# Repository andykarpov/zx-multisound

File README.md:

## ZX-MultiSound
Sound card for ZX Spectrum (NemoBus).

### Tech specs
* TurboSound FM (2xYM2203)
* General Sound (16MHz, 1024Kb of RAM)
* SAA1099 (use port #FF/#1FF to access SAA chip, write #F7/#FF to #FFFD port to enable/disable SAA)
* SounDrive (ports #0F, #1F, #4F, #5F)
* MIDI synthesizer (controlled via YM(AY) chip - compatible with ZX Spectrum 128K / ZXUNO)
* Low profile PCB: 170x64mm
* 5V and 12V power required
* 4x 1-bit digital DACs for GS and SounDrive

### Changelog & current status
* Rev.A - first release. Please note the [errata](pcb/rev.A/ERRATA.txt);
* Rev.A1 - fixed known rev.A issues. Please note the [errata](pcb/rev.A1/ERRATA.txt).
* Rev.A2:
    * Fixed Z80 clocking - added buffer;
    * Fixed 3.5mm jack footprint swapped left-right channels;
    * Fixed misplaced R20 and R34 labels on silkscreen;
    * 74LVC1G125DB replaced by 74AHCT1G125DB;
    * C3,C5,C17,C18 slightly moved left;
    * Added ledge on edge connector;
    * Improved SAM2695 footprint for hand soldering.
* Rev.KA2:
    * Single SRAM chip 2mb

Sound card has been tested only with ZX Evolution. You can use it with another computer at your own risk.

### Related projects
* Turbo Sound FM - [link](http://www.nedopc.com/TURBOSOUND/ts-fm.php)
* ZXM-SoundCard - [link](http://micklab.ru/My%20Soundcard/ZXMSoundCard.htm)
* ZXM-GeneralSound - [link](http://micklab.ru/My%20Soundcard/ZXMGeneralSound.htm)
* NeoGS - [link](http://www.nedopc.com/gs/ngs.php)

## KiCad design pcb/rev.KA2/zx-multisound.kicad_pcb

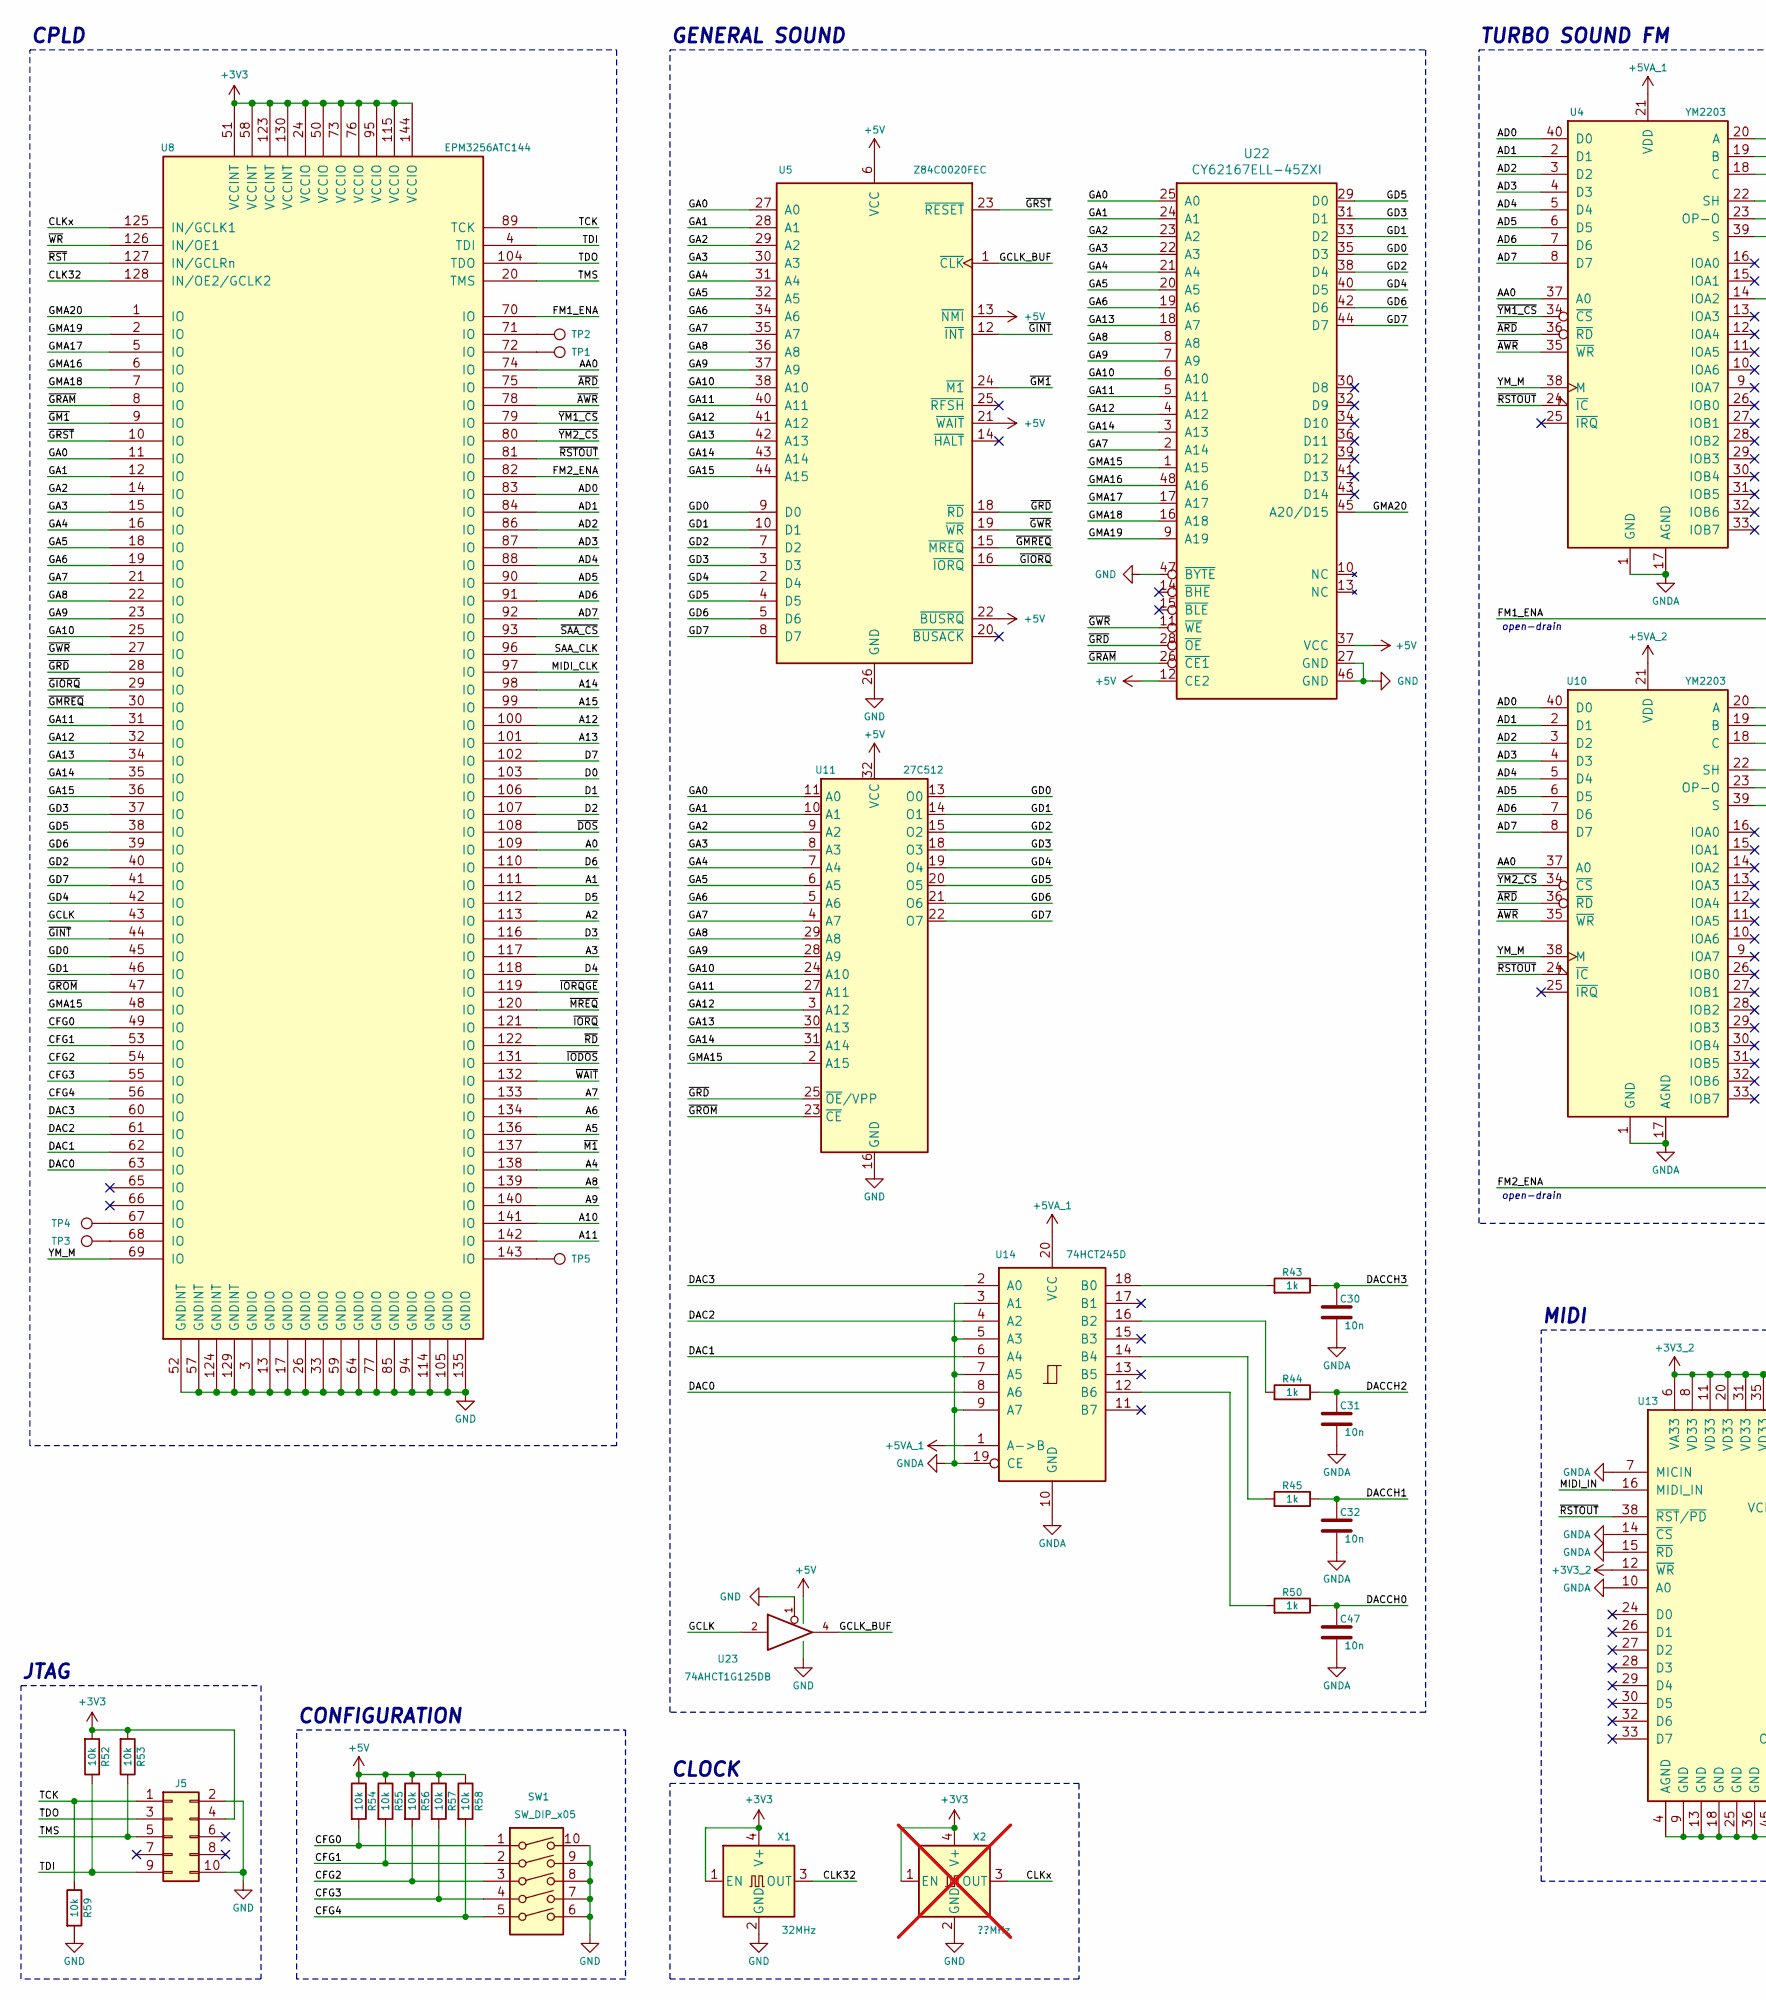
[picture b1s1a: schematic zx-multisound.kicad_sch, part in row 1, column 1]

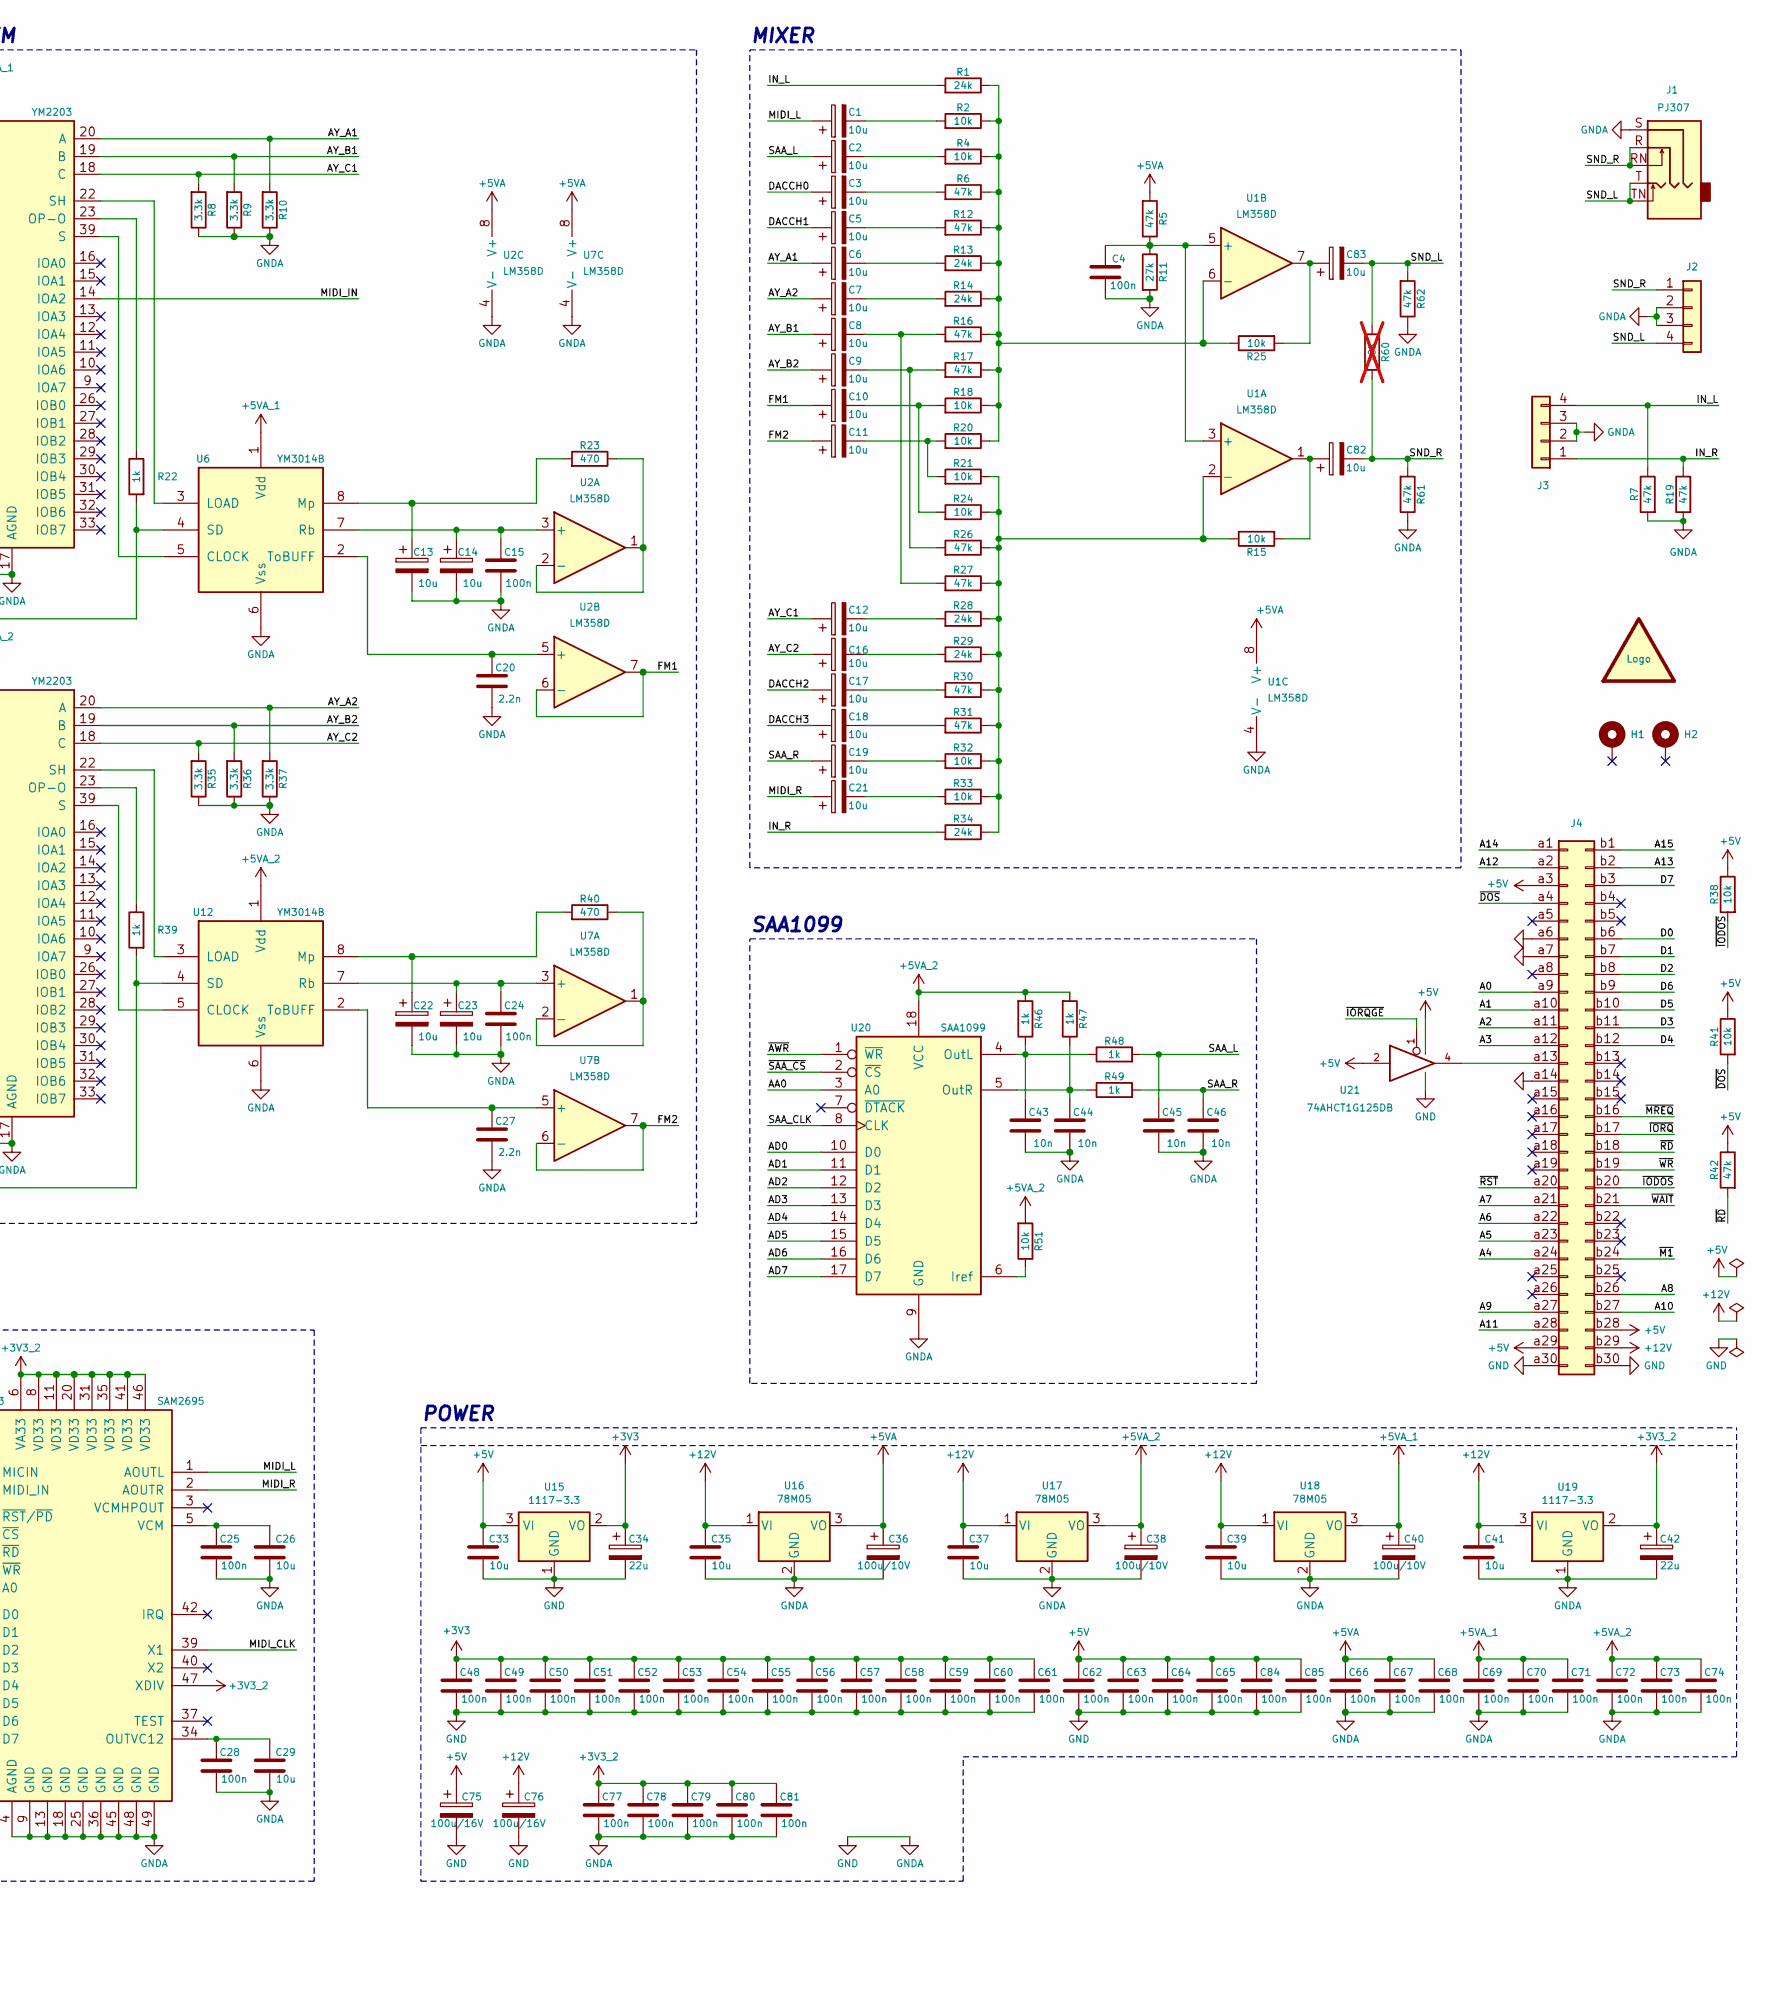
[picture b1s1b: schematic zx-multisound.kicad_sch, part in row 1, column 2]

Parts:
C1, C2, C3, C5, C6, C7, C8, C9, C10, C11, C12, C13, C14, C16, C17, C18, C19, C21, C22, C23, C82, C83: 10u; CP_Elec_4x5.4
C4, C15, C24, C25, C28, C48, C49, C50, C51, C52, C53, C54, C55, C56, C57, C58, C59, C60, C61, C62, C63, C64, C65, C66, C67, C68, C69, C70, C71, C72, C73, C74, C77, C78, C79, C80, C81, C84, C85: 100n; C_0805_2012Metric_Pad1.18x1.45mm_HandSolder
C20, C27: 2.2n; C_0805_2012Metric_Pad1.18x1.45mm_HandSolder
C26, C29, C33, C35, C37, C39, C41: 10u; C_1206_3216Metric_Pad1.33x1.80mm_HandSolder
C30, C31, C32, C43, C44, C45, C46, C47: 10n; C_0805_2012Metric_Pad1.18x1.45mm_HandSolder
C34, C42: 22u; CP_EIA-3216-18_Kemet-A_Pad1.58x1.35mm_HandSolder
C36, C38, C40: 100u/10V; CP_EIA-6032-28_Kemet-C_Pad2.25x2.35mm_HandSolder
C75, C76: 100u/16V; CP_Elec_6.3x7.7
H1, H2: MountingHole_Pad; MountingHole_2.7mm_M2.5_DIN965_Pad
J1: PJ307; PJ-307
J2, J3: Conn_01x04; PinHeader_1x04_P2.54mm_Vertical
J4: Conn_02x30_Row_Letter_First; ZX_NEMO_60_EDGE
J5: Conn_02x05_Odd_Even; PinHeader_2x05_P2.54mm_Vertical
LOGO1: graphic; black-mage-12.5x8.6
R1, R13, R14, R28, R29, R34: 24k; R_0805_2012Metric_Pad1.20x1.40mm_HandSolder
R2, R4, R15, R18, R20, R21, R24, R25, R32, R33, R38, R41, R51, R52, R53, R54, R55, R56, R57, R58, R59: 10k; R_0805_2012Metric_Pad1.20x1.40mm_HandSolder
R5, R6, R7, R12, R16, R17, R19, R26, R27, R30, R31, R42, R61, R62: 47k; R_0805_2012Metric_Pad1.20x1.40mm_HandSolder
R8, R9, R10, R35, R36, R37: 3.3k; R_0805_2012Metric_Pad1.20x1.40mm_HandSolder
R11: 27k; R_0805_2012Metric_Pad1.20x1.40mm_HandSolder
R22, R39, R43, R44, R45, R46, R47, R48, R49, R50: 1k; R_0805_2012Metric_Pad1.20x1.40mm_HandSolder
R23, R40: 470; R_0805_2012Metric_Pad1.20x1.40mm_HandSolder
R60: 10K; R_0805_2012Metric_Pad1.20x1.40mm_HandSolder; not fitted
SW1: SW_DIP_x05; SW_DIP_SPSTx05_Slide_6.7x14.26mm_W7.62mm_P2.54mm_LowProfile
TP1, TP2, TP3, TP4, TP5: TestPoint; TestPoint_Pad_D1.0mm
U1, U2, U7: LM358D; SOIC-8_3.9x4.9mm_P1.27mm
U4, U10: YM2203; DIP-40_W15.24mm_Socket
U5: Z84C0020FEC; TQFP-44_14x14mm_P0.8mm
U6, U12: YM3014B; DIP-8_W7.62mm_Socket
U8: EPM3256ATC144; TQFP-144_20x20mm_P0.5mm
U11: 27C512; PLCC-32_11.4x14.0mm_P1.27mm-longpads
U13: SAM2695; QFN-48-1EP_6x6mm_P0.4mm_EP4.2x4.2mm
U14: 74HCT245D; SOIC-20W_7.5x12.8mm_P1.27mm
U15, U19: 1117-3.3; SOT-223-3_TabPin2
U16, U17, U18: 78M05; TO-252-2
U20: SAA1099; DIP-18_W7.62mm_Socket
U21, U23: 74AHCT1G125DB; SOT-23-5_HandSoldering
U22: CY62167ELL-45ZXI; TSOP-I-48_18.4x12mm_P0.5mm
X1: 32MHz; Oscillator_SMD_7050_7.0x5.0mm
X2: ??MHz; Oscillator_SMD_7050_7.0x5.0mm; not fitted

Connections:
+3V3: C34.1, C48.1, C49.1, C50.1, C51.1, C52.1, C53.1, C54.1, C55.1, C56.1, C57.1, C58.1, C59.1, C60.2, C61.2, J5.4, R52.2, R53.2, U8.24 (VCCIO), U8.50 (VCCIO), U8.51 (VCCINT), U8.58 (VCCINT), U8.73 (VCCIO), U8.76 (VCCIO), U8.95 (VCCIO), U8.115 (VCCIO), U8.123 (VCCINT), U8.130 (VCCINT), U8.144 (VCCIO), U15.2 (VO), X1.1 (EN), X1.4 (V+), X2.1 (EN), X2.4 (V+)
+3V3_2: C42.1, C77.1, C78.1, C79.1, C80.1, C81.1, U13.6 (VA33), U13.8 (VD33), U13.11 (VD33), U13.12 (~WR), U13.20 (VD33), U13.31 (VD33), U13.35 (VD33), U13.41 (VD33), U13.46 (VD33), U13.47 (XDIV), U19.2 (VO)
+5V: C33.1, C62.2, C63.2, C64.2, C65.2, C75.1, C84.2, C85.2, J4.a3, J4.a29, J4.b28, R38.1, R41.1, R42.1, R54.1, R55.1, R56.1, R57.1, R58.1, U5.6 (VCC), U5.13 (~NMI), U5.21 (~WAIT), U5.22 (~BUSRQ), U11.32 (VCC), U15.3 (VI), U21.2, U21.5 (VCC), U22.12 (CE2), U22.37 (VCC), U23.5 (VCC)
+5VA: C36.1, C66.2, C67.2, C68.2, R5.2, U1.8 (V+), U2.8 (V+), U7.8 (V+), U16.3 (VO)
+5VA_1: C40.1, C69.2, C70.2, C71.2, U4.21 (VDD), U6.1 (Vdd), U14.1 (A->B), U14.20 (VCC), U18.3 (VO)
+5VA_2: C38.1, C72.2, C73.2, C74.2, R46.2, R47.2, R51.2, U10.21 (VDD), U12.1 (Vdd), U17.3 (VO), U20.18 (VCC)
+12V: C35.1, C37.1, C39.1, C41.1, C76.1, J4.b29, U16.1 (VI), U17.1 (VI), U18.1 (VI), U19.3 (VI)
/A0: J4.a9, U8.109 (IO)
/A1: J4.a10, U8.111 (IO)
/A2: J4.a11, U8.113 (IO)
/A3: J4.a12, U8.117 (IO)
/A4: J4.a24, U8.138 (IO)
/A5: J4.a23, U8.136 (IO)
/A6: J4.a22, U8.134 (IO)
/A7: J4.a21, U8.133 (IO)
/A8: J4.b26, U8.139 (IO)
/A9: J4.a27, U8.140 (IO)
/A10: J4.b27, U8.141 (IO)
/A11: J4.a28, U8.142 (IO)
/A12: J4.a2, U8.100 (IO)
/A13: J4.b2, U8.101 (IO)
/A14: J4.a1, U8.98 (IO)
/A15: J4.b1, U8.99 (IO)
/AA0: U4.37 (A0), U8.74 (IO), U10.37 (A0), U20.3 (A0)
/AD0: U4.40 (D0), U8.83 (IO), U10.40 (D0), U20.10 (D0)
/AD1: U4.2 (D1), U8.84 (IO), U10.2 (D1), U20.11 (D1)
/AD2: U4.3 (D2), U8.86 (IO), U10.3 (D2), U20.12 (D2)
/AD3: U4.4 (D3), U8.87 (IO), U10.4 (D3), U20.13 (D3)
/AD4: U4.5 (D4), U8.88 (IO), U10.5 (D4), U20.14 (D4)
/AD5: U4.6 (D5), U8.90 (IO), U10.6 (D5), U20.15 (D5)
/AD6: U4.7 (D6), U8.91 (IO), U10.7 (D6), U20.16 (D6)
/AD7: U4.8 (D7), U8.92 (IO), U10.8 (D7), U20.17 (D7)
/AY_A1: C6.1, R10.2, U4.20 (A)
/AY_A2: C7.1, R37.2, U10.20 (A)
/AY_B1: C8.1, R9.2, U4.19 (B)
/AY_B2: C9.1, R36.2, U10.19 (B)
/AY_C1: C12.1, R8.2, U4.18 (C)
/AY_C2: C16.1, R35.2, U10.18 (C)
/CFG0: R54.2, SW1.1, U8.49 (IO)
/CFG1: R55.2, SW1.2, U8.53 (IO)
/CFG2: R56.2, SW1.3, U8.54 (IO)
/CFG3: R57.2, SW1.4, U8.55 (IO)
/CFG4: R58.2, SW1.5, U8.56 (IO)
/CLK32: U8.128 (IN/OE2/GCLK2), X1.3 (OUT)
/CLKx: U8.125 (IN/GCLK1), X2.3 (OUT)
/D0: J4.b6, U8.103 (IO)
/D1: J4.b7, U8.106 (IO)
/D2: J4.b8, U8.107 (IO)
/D3: J4.b11, U8.116 (IO)
/D4: J4.b12, U8.118 (IO)
/D5: J4.b10, U8.112 (IO)
/D6: J4.b9, U8.110 (IO)
/D7: J4.b3, U8.102 (IO)
/DAC0: U8.63 (IO), U14.8 (A6)
/DAC1: U8.62 (IO), U14.6 (A4)
/DAC2: U8.61 (IO), U14.4 (A2)
/DAC3: U8.60 (IO), U14.2 (A0)
/DACCH0: C3.1, C47.1, R50.1
/DACCH1: C5.1, C32.1, R45.1
/DACCH2: C17.1, C31.1, R44.1
/DACCH3: C18.1, C30.1, R43.1
/FM1: C10.1, U2.6 (-), U2.7
/FM1_ENA: R22.2, U6.4 (SD), U8.70 (IO)
/FM2: C11.1, U7.6 (-), U7.7
/FM2_ENA: R39.2, U8.82 (IO), U12.4 (SD)
/GA0: U5.27 (A0), U8.11 (IO), U11.11 (A0), U22.25 (A0)
/GA1: U5.28 (A1), U8.12 (IO), U11.10 (A1), U22.24 (A1)
/GA2: U5.29 (A2), U8.14 (IO), U11.9 (A2), U22.23 (A2)
/GA3: U5.30 (A3), U8.15 (IO), U11.8 (A3), U22.22 (A3)
/GA4: U5.31 (A4), U8.16 (IO), U11.7 (A4), U22.21 (A4)
/GA5: U5.32 (A5), U8.18 (IO), U11.6 (A5), U22.20 (A5)
/GA6: U5.34 (A6), U8.19 (IO), U11.5 (A6), U22.19 (A6)
/GA7: U5.35 (A7), U8.21 (IO), U11.4 (A7), U22.2 (A14)
/GA8: U5.36 (A8), U8.22 (IO), U11.29 (A8), U22.8 (A8)
/GA9: U5.37 (A9), U8.23 (IO), U11.28 (A9), U22.7 (A9)
/GA10: U5.38 (A10), U8.25 (IO), U11.24 (A10), U22.6 (A10)
/GA11: U5.40 (A11), U8.31 (IO), U11.27 (A11), U22.5 (A11)
/GA12: U5.41 (A12), U8.32 (IO), U11.3 (A12), U22.4 (A12)
/GA13: U5.42 (A13), U8.34 (IO), U11.30 (A13), U22.18 (A7)
/GA14: U5.43 (A14), U8.35 (IO), U11.31 (A14), U22.3 (A13)
/GA15: U5.44 (A15), U8.36 (IO)
/GCLK: U8.43 (IO), U23.2
/GCLK_BUF: U5.1 (~CLK), U23.4
/GD0: U5.9 (D0), U8.45 (IO), U11.13 (O0), U22.35 (D3)
/GD1: U5.10 (D1), U8.46 (IO), U11.14 (O1), U22.33 (D2)
/GD2: U5.7 (D2), U8.40 (IO), U11.15 (O2), U22.38 (D4)
/GD3: U5.3 (D3), U8.37 (IO), U11.18 (O3), U22.31 (D1)
/GD4: U5.2 (D4), U8.42 (IO), U11.19 (O4), U22.40 (D5)
/GD5: U5.4 (D5), U8.38 (IO), U11.20 (O5), U22.29 (D0)
/GD6: U5.5 (D6), U8.39 (IO), U11.21 (O6), U22.42 (D6)
/GD7: U5.8 (D7), U8.41 (IO), U11.22 (O7), U22.44 (D7)
/GMA15: U8.48 (IO), U11.2 (A15), U22.1 (A15)
/GMA16: U8.6 (IO), U22.48 (A16)
/GMA17: U8.5 (IO), U22.17 (A17)
/GMA18: U8.7 (IO), U22.16 (A18)
/GMA19: U8.2 (IO), U22.9 (A19)
/GMA20: U8.1 (IO), U22.45 (A20/D15)
/IN_L: J3.4, R1.2, R7.1
/IN_R: J3.1, R19.1, R34.2
/MIDI_CLK: U8.97 (IO), U13.39 (X1)
/MIDI_IN: U4.14 (IOA2), U13.16 (MIDI_IN)
/MIDI_L: C1.1, U13.1 (AOUTL)
/MIDI_R: C21.1, U13.2 (AOUTR)
/SAA_CLK: U8.96 (IO), U20.8 (CLK)
/SAA_L: C2.1, C45.1, R48.2
/SAA_R: C19.1, C46.1, R49.2
/SND_L: C83.2, J1.T, J1.TN, J2.4, R60.2, R62.2
/SND_R: C82.2, J1.R, J1.RN, J2.1, R60.1, R61.2
/TCK: J5.1, R59.1, U8.89 (TCK)
/TDI: J5.9, R52.1, U8.4 (TDI)
/TDO: J5.3, U8.104 (TDO)
/TMS: J5.5, R53.1, U8.20 (TMS)
/YM_M: U4.38 (M), U8.69 (IO), U10.38 (M)
/~ARD: U4.36 (~RD), U8.75 (IO), U10.36 (~RD)
/~AWR: U4.35 (~WR), U8.78 (IO), U10.35 (~WR), U20.1 (~WR)
/~DOS: J4.a4, R41.2, U8.108 (IO)
/~GINT: U5.12 (~INT), U8.44 (IO)
/~GIORQ: U5.16 (~IORQ), U8.29 (IO)
/~GM1: U5.24 (~M1), U8.9 (IO)
/~GMREQ: U5.15 (~MREQ), U8.30 (IO)
/~GRAM: U8.8 (IO), U22.26 (~CE1)
/~GRD: U5.18 (~RD), U8.28 (IO), U11.25 (~OE/VPP), U22.28 (~OE)
/~GROM: U8.47 (IO), U11.23 (~CE)
/~GRST: U5.23 (~RESET), U8.10 (IO)
/~GWR: U5.19 (~WR), U8.27 (IO), U22.11 (~WE)
/~IODOS: J4.b20, R38.2, U8.131 (IO)
/~IORQGE: U8.119 (IO), U21.1
/~IORQ: J4.b17, U8.121 (IO)
/~M1: J4.b24, U8.137 (IO)
/~MREQ: J4.b16, U8.120 (IO)
/~RD: J4.b18, R42.2, U8.122 (IO)
/~RSTOUT: U4.24 (~IC), U8.81 (IO), U10.24 (~IC), U13.38 (~RST/~PD)
/~RST: J4.a20, U8.127 (IN/GCLRn)
/~SAA_CS: U8.93 (IO), U20.2 (~CS)
/~WAIT: J4.b21, U8.132 (IO)
/~WR: J4.b19, U8.126 (IN/OE1)
/~YM1_CS: U4.34 (~CS), U8.79 (IO)
/~YM2_CS: U8.80 (IO), U10.34 (~CS)
GND: C4.1, C13.2, C14.2, C15.2, C20.2, C22.2, C23.2, C24.2, C25.2, C26.2, C27.2, C28.2, C29.2, C30.2, C31.2, C32.2, C33.2, C34.2, C35.2, C36.2, C37.2, C38.2, C39.2, C40.2, C41.2, C42.2, C43.2, C44.2, C45.2, C46.2, C47.2, C48.2, C49.2, C50.2, C51.2, C52.2, C53.2, C54.2, C55.2, C56.2, C57.2, C58.2, C59.2, C60.1, C61.1, C62.1, C63.1, C64.1, C65.1, C66.1, C67.1, C68.1, C69.1, C70.1, C71.1, C72.1, C73.1, C74.1, C75.2, C76.2, C77.2, C78.2, C79.2, C80.2, C81.2, C84.1, C85.1, J1.S, J2.2, J2.3, J3.2, J3.3, J4.a6, J4.a7, J4.a14, J4.a30, J4.b30, J5.2, J5.10, R7.2, R8.1, R9.1, R10.1, R11.2, R19.2, R35.1, R36.1, R37.1, R59.2, R61.1, R62.1, SW1.6, SW1.7, SW1.8, SW1.9, SW1.10, U1.4 (V-), U2.4 (V-), U4.1 (GND), U4.17 (AGND), U5.26 (GND), U6.6 (Vss), U7.4 (V-), U8.3 (GNDIO), U8.13 (GNDIO), U8.17 (GNDIO), U8.26 (GNDIO), U8.33 (GNDIO), U8.52 (GNDINT), U8.57 (GNDINT), U8.59 (GNDIO), U8.64 (GNDIO), U8.77 (GNDIO), U8.85 (GNDIO), U8.94 (GNDIO), U8.105 (GNDIO), U8.114 (GNDIO), U8.124 (GNDINT), U8.129 (GNDINT), U8.135 (GNDIO), U10.1 (GND), U10.17 (AGND), U11.16 (GND), U12.6 (Vss), U13.4 (AGND), U13.7 (MICIN), U13.9 (GND), U13.10 (A0), U13.13 (GND), U13.14 (~CS), U13.15 (~RD), U13.18 (GND), U13.25 (GND), U13.36 (GND), U13.45 (GND), U13.48 (GND), U13.49 (GND), U14.3 (A1), U14.5 (A3), U14.7 (A5), U14.9 (A7), U14.10 (GND), U14.19 (CE), U15.1 (GND), U16.2 (GND), U17.2 (GND), U18.2 (GND), U19.1 (GND), U20.9 (GND), U21.3 (GND), U22.27 (GND), U22.46 (GND), U22.47 (~BYTE), U23.1, U23.3 (GND), X1.2 (GND), X2.2 (GND)
unnamed: C1.2, R2.2
unnamed: C2.2, R4.2
unnamed: C3.2, R6.2
unnamed: C5.2, R12.2
unnamed: C6.2, R13.2
unnamed: C7.2, R14.2
unnamed: C8.2, R16.2, R27.2
unnamed: C9.2, R17.2, R26.2
unnamed: C10.2, R18.2, R24.2
unnamed: C11.2, R20.2, R21.2
unnamed: C12.2, R28.2
unnamed: C16.2, R29.2
unnamed: C17.2, R30.2
unnamed: C18.2, R31.2
unnamed: C19.2, R32.2
unnamed: C21.2, R33.2
unnamed: C82.1, R15.2, U1.1
unnamed: C83.1, R25.2, U1.7
unnamed: J4.a13, U21.4
unnamed: TP1.1 (1_1), U8.72 (IO)
unnamed: TP2.1 (1_1), U8.71 (IO)
unnamed: TP3.1 (1_1), U8.68 (IO)
unnamed: TP4.1 (1_1), U8.67 (IO)
unnamed: TP5.1 (1_1), U8.143 (IO)
unnamed: C4.2, R5.1, R11.1, U1.3 (+), U1.5 (+)
unnamed: R15.1, R21.1, R24.1, R26.1, R27.1, R28.1, R29.1, R30.1, R31.1, R32.1, R33.1, R34.1, U1.2 (-)
unnamed: R1.1, R2.1, R4.1, R6.1, R12.1, R13.1, R14.1, R16.1, R17.1, R18.1, R20.1, R25.1, U1.6 (-)
unnamed: C14.1, C15.1, U2.3 (+), U6.7 (Rb)
unnamed: R23.1, U2.1, U2.2 (-)
unnamed: C20.1, U2.5 (+), U6.2 (ToBUFF)
unnamed: R22.1, U4.23 (OP-O)
unnamed: U4.39 (S), U6.5 (CLOCK)
unnamed: U4.22 (SH), U6.3 (LOAD)
unnamed: C13.1, R23.2, U6.8 (Mp)
unnamed: R40.1, U7.1, U7.2 (-)
unnamed: R39.1, U10.23 (OP-O)
unnamed: U10.39 (S), U12.5 (CLOCK)
unnamed: U10.22 (SH), U12.3 (LOAD)
unnamed: C22.1, R40.2, U12.8 (Mp)
unnamed: C23.1, C24.1, U7.3 (+), U12.7 (Rb)
unnamed: C27.1, U7.5 (+), U12.2 (ToBUFF)
unnamed: C28.1, C29.1, U13.34 (OUTVC12)
unnamed: C25.1, C26.1, U13.5 (VCM)
unnamed: R43.2, U14.18 (B0)
unnamed: R44.2, U14.16 (B2)
unnamed: R45.2, U14.14 (B4)
unnamed: R50.2, U14.12 (B6)
unnamed: R51.1, U20.6 (Iref)
unnamed: C43.1, R46.1, R48.1, U20.4 (OutL)
unnamed: C44.1, R47.1, R49.1, U20.5 (OutR)

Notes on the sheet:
SAA1099
CONFIGURATION
open-drain
GENERAL SOUND
TURBO SOUND FM
MIXER
CPLD
JTAG
POWER
MIDI
CLOCK

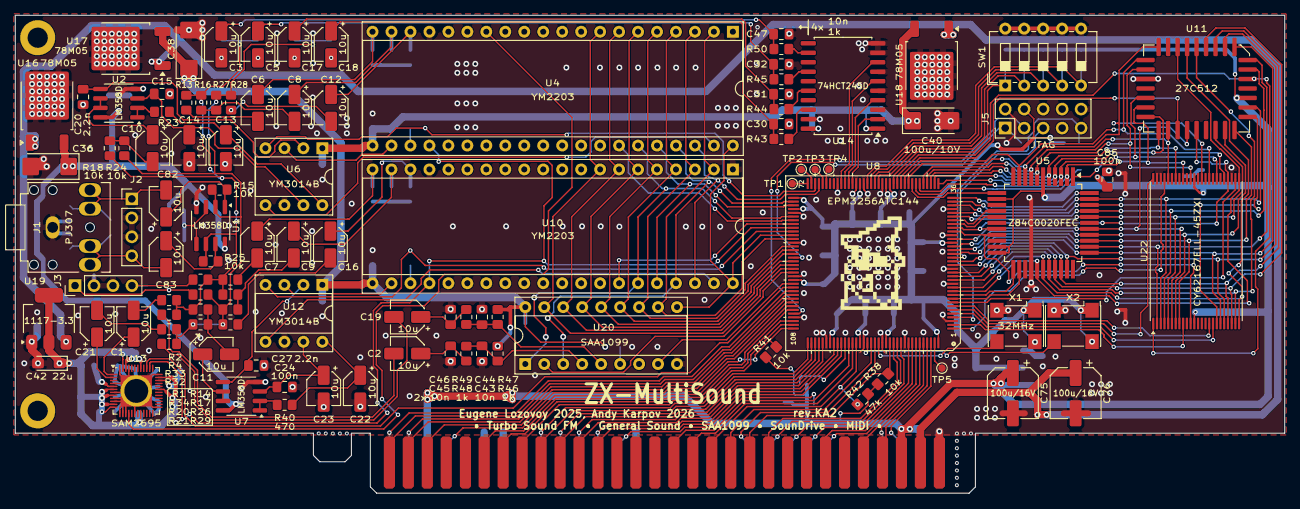
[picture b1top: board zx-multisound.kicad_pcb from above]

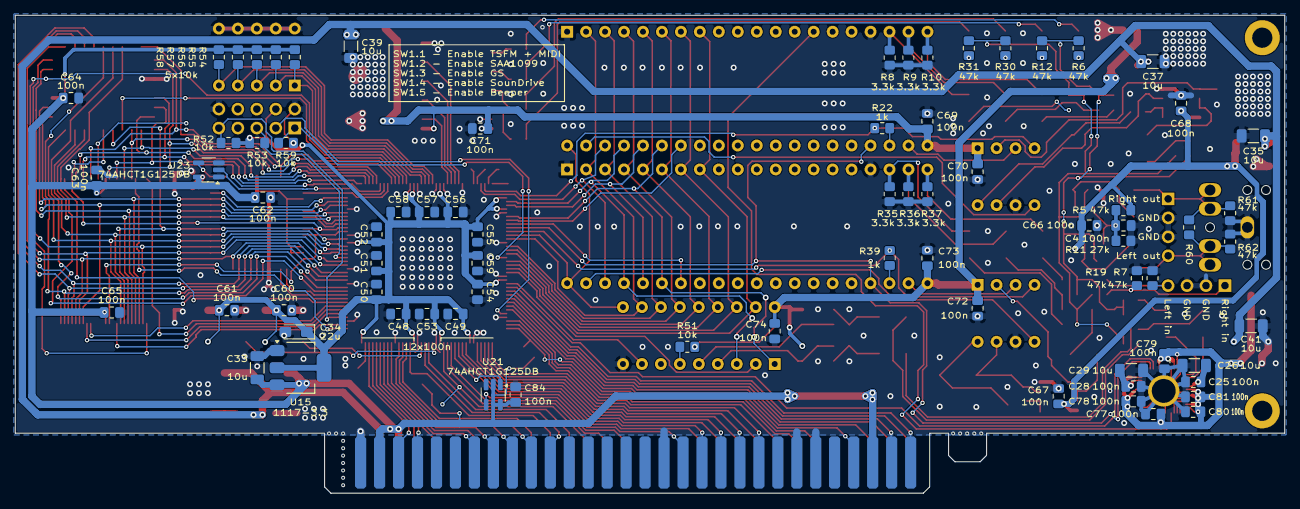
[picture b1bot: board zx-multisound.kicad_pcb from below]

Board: 2 copper layers, 170.0 x 64.0 mm, 183 parts (75 on the bottom side), 189 nets.

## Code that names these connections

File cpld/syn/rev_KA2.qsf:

# -------------------------------------------------------------------------- #
#
# Copyright (C) 1991-2013 Altera Corporation
# Your use of Altera Corporation's design tools, logic functions 
# and other software and tools, and its AMPP partner logic 
# functions, and any output files from any of the foregoing 
# (including device programming or simulation files), and any 
# associated documentation or information are expressly subject 
# to the terms and conditions of the Altera Program License 
# Subscription Agreement, Altera MegaCore Function License 
# Agreement, or other applicable license agreement, including, 
# without limitation, that your use is for the sole purpose of 
# programming logic devices manufactured by Altera and sold by 
# Altera or its authorized distributors.  Please refer to the 
# applicable agreement for further details.
#
# -------------------------------------------------------------------------- #
#
# Quartus II 64-Bit
# Version 13.0.1 Build 232 06/12/2013 Service Pack 1 SJ Full Version
# Date created = 12:04:27  October 04, 2020
#
# -------------------------------------------------------------------------- #
#
# Notes:
#
# 1) The default values for assignments are stored in the file:
#		zx_multisound_assignment_defaults.qdf
#    If this file doesn't exist, see file:
#		assignment_defaults.qdf
#
# 2) Altera recommends that you do not modify this file. This
#    file is updated automatically by the Quartus II software
#    and any changes you make may be lost or overwritten.
#
# -------------------------------------------------------------------------- #


set_global_assignment -name FAMILY MAX3000A
set_global_assignment -name DEVICE "EPM3256ATC144-10"
set_global_assignment -name TOP_LEVEL_ENTITY zx_multisound
set_global_assignment -name ORIGINAL_QUARTUS_VERSION "13.0 SP1"
set_global_assignment -name PROJECT_CREATION_TIME_DATE "12:04:27  OCTOBER 04, 2020"
set_global_assignment -name LAST_QUARTUS_VERSION "13.0 SP1"
set_global_assignment -name PROJECT_OUTPUT_DIRECTORY output
set_global_assignment -name DEVICE_FILTER_PIN_COUNT 144
set_global_assignment -name ERROR_CHECK_FREQUENCY_DIVISOR "-1"
set_global_assignment -name SDC_FILE clocks.sdc
set_global_assignment -name VERILOG_FILE ../rtl/top.v
set_global_assignment -name VHDL_INPUT_VERSION VHDL_2008
set_global_assignment -name VHDL_SHOW_LMF_MAPPING_MESSAGES OFF
set_global_assignment -name VERILOG_INPUT_VERSION SYSTEMVERILOG_2005
set_global_assignment -name VERILOG_SHOW_LMF_MAPPING_MESSAGES OFF
set_global_assignment -name MAX7000_DEVICE_IO_STANDARD "3.3-V LVTTL"
set_global_assignment -name SAVE_DISK_SPACE OFF
set_global_assignment -name TIMEQUEST_MULTICORNER_ANALYSIS OFF
set_global_assignment -name SYNTH_TIMING_DRIVEN_SYNTHESIS OFF

set_location_assignment PIN_5 -to gma[17]
set_location_assignment PIN_6 -to gma[16]
set_location_assignment PIN_7 -to gma[18]
set_location_assignment PIN_2 -to gma[19]
set_location_assignment PIN_1 -to gma[20]
set_location_assignment PIN_8 -to n_gram
set_location_assignment PIN_9 -to n_gm1
set_location_assignment PIN_10 -to n_grst
set_location_assignment PIN_11 -to ga[0]
set_location_assignment PIN_12 -to ga[1]
set_location_assignment PIN_14 -to ga[2]
set_location_assignment PIN_15 -to ga[3]
set_location_assignment PIN_16 -to ga[4]
set_location_assignment PIN_18 -to ga[5]
set_location_assignment PIN_19 -to ga[6]
set_location_assignment PIN_21 -to ga[7]
set_location_assignment PIN_22 -to ga[8]
set_location_assignment PIN_23 -to ga[9]
set_location_assignment PIN_25 -to ga[10]
set_location_assignment PIN_27 -to n_gwr
set_location_assignment PIN_28 -to n_grd
set_location_assignment PIN_29 -to n_giorq
set_location_assignment PIN_30 -to n_gmreq
set_location_assignment PIN_31 -to ga[11]
set_location_assignment PIN_32 -to ga[12]
set_location_assignment PIN_34 -to ga[13]
set_location_assignment PIN_35 -to ga[14]
set_location_assignment PIN_36 -to ga[15]
set_location_assignment PIN_37 -to gd[3]
set_location_assignment PIN_38 -to gd[5]
set_location_assignment PIN_39 -to gd[6]
set_location_assignment PIN_40 -to gd[2]
set_location_assignment PIN_41 -to gd[7]
set_location_assignment PIN_42 -to gd[4]
set_location_assignment PIN_43 -to gclk
set_location_assignment PIN_44 -to n_gint
set_location_assignment PIN_45 -to gd[0]
set_location_assignment PIN_46 -to gd[1]
set_location_assignment PIN_47 -to n_grom
set_location_assignment PIN_48 -to gma[15]
set_location_assignment PIN_49 -to cfg[0]
set_location_assignment PIN_53 -to cfg[1]
set_location_assignment PIN_54 -to cfg[2]
set_location_assignment PIN_55 -to cfg[3]
set_location_assignment PIN_56 -to cfg[4]
set_location_assignment PIN_60 -to dac3_out
set_location_assignment PIN_61 -to dac2_out
set_location_assignment PIN_62 -to dac1_out
set_location_assignment PIN_63 -to dac0_out
set_location_assignment PIN_69 -to ym_m
set_location_assignment PIN_70 -to fm1_ena
set_location_assignment PIN_74 -to aa0
set_location_assignment PIN_75 -to n_ard
set_location_assignment PIN_78 -to n_awr
set_location_assignment PIN_79 -to n_ym1_cs
set_location_assignment PIN_80 -to n_ym2_cs
set_location_assignment PIN_81 -to n_rstout
set_location_assignment PIN_82 -to fm2_ena
set_location_assignment PIN_83 -to ad[0]
set_location_assignment PIN_84 -to ad[1]
set_location_assignment PIN_86 -to ad[2]
set_location_assignment PIN_87 -to ad[3]
set_location_assignment PIN_88 -to ad[4]
set_location_assignment PIN_90 -to ad[5]
set_location_assignment PIN_91 -to ad[6]
set_location_assignment PIN_92 -to ad[7]
set_location_assignment PIN_93 -to n_saa_cs
set_location_assignment PIN_96 -to saa_clk
set_location_assignment PIN_97 -to midi_clk
set_location_assignment PIN_98 -to a[14]
set_location_assignment PIN_99 -to a[15]
set_location_assignment PIN_100 -to a[12]
set_location_assignment PIN_101 -to a[13]
set_location_assignment PIN_102 -to d[7]
set_location_assignment PIN_103 -to d[0]
set_location_assignment PIN_106 -to d[1]
set_location_assignment PIN_107 -to d[2]
set_location_assignment PIN_108 -to n_dos
set_location_assignment PIN_109 -to a[0]
set_location_assignment PIN_110 -to d[6]
set_location_assignment PIN_111 -to a[1]
set_location_assignment PIN_112 -to d[5]
set_location_assignment PIN_113 -to a[2]
set_location_assignment PIN_116 -to d[3]
set_location_assignment PIN_117 -to a[3]
set_location_assignment PIN_118 -to d[4]
set_location_assignment PIN_119 -to n_iorqge
set_location_assignment PIN_120 -to n_mreq
set_location_assignment PIN_121 -to n_iorq
set_location_assignment PIN_122 -to n_rd
set_location_assignment PIN_125 -to clkx
set_location_assignment PIN_126 -to n_wr
set_location_assignment PIN_127 -to rst_n
set_location_assignment PIN_128 -to clk32
set_location_assignment PIN_131 -to n_iodos
set_location_assignment PIN_132 -to n_wait
set_location_assignment PIN_133 -to a[7]
set_location_assignment PIN_134 -to a[6]
set_location_assignment PIN_136 -to a[5]
set_location_assignment PIN_137 -to n_m1
set_location_assignment PIN_138 -to a[4]
set_location_assignment PIN_139 -to a[8]
set_location_assignment PIN_140 -to a[9]
set_location_assignment PIN_141 -to a[10]
set_location_assignment PIN_142 -to a[11]
set_global_assignment -name MAX7000_OPTIMIZATION_TECHNIQUE BALANCED
set_global_assignment -name PRE_MAPPING_RESYNTHESIS OFF
set_global_assignment -name OPTIMIZE_HOLD_TIMING OFF
set_global_assignment -name OPTIMIZE_MULTI_CORNER_TIMING ON
set_global_assignment -name FITTER_EFFORT "STANDARD FIT"
set_global_assignment -name RESERVE_ALL_UNUSED_PINS_NO_OUTPUT_GND "AS INPUT TRI-STATED"

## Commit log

2026-04-02 rev.KA2
2026-04-02 CPLD firmware for rev.KA2
2026-04-02 Added beeper
2026-04-02 Added label about SW[4]
2026-04-02 Added renders of the Rev.KA2
2026-04-02 Updated 3D models, embed into the project
2026-05-13 Revert "Added beeper"
    This reverts commit b16418dcb5032fdd0553d0450ffd3fbb3b677569.
2026-05-13 Removed pcb history
2026-05-13 cleanup
